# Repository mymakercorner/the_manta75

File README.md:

# The Manta75

The Manta75 is an exploded arrows and nav clusters 75% keyboard with a curvy bottom.
It is the second project of the *Sea Collection* and as such it's name is taken from one of the species we see in our oceans, the [Manta ray](https://en.wikipedia.org/wiki/Manta_ray).

The [Satisfaction 75](https://cannonkeys.com/collections/satisfaction-75) have this similar exploded arrows/nav clusters, on the manta75 I went with no knob and screen to maximize the number of available keys.

## Features

- Two pieces case designed with Fusion360.
- PCB designed with Kicad 5.1.5.
- Bottom mount leaf spring plate design with optional friction fit gaskets.
- [Unified C3 daughterboard](https://github.com/ai03-2725/Unified-Daughterboard)
- QMK firmware with VIA and VIAL support.

## Layout options

## Specifications

- Typing angle: 6 degrees
- Width: ~346mm
- Height: ~150mm
- Bezels size: 15mm all around.
- Front height: 18.3mm without bumpons, 19.7mm with bumpons.
- Top plate to top case distance: 7mm.
- Bumpons: 3M (reference SJ-5382). 
- Weight:
    - Aluminium top and bottom case: ~1,46Kg
    - Alumininum top and copper bottom case: ~4Kg
- Screws:
    - 6X M2.5x10 screws for top/bottom parts.
    - 4X M2.5x4 screws for plate/bottom parts.
    - 4X M2x4 screws for USB daughterboard. 

## Licensing 

[![CC BY 4.0][cc-by-shield]][cc-by]

Hardware design is provided under the very permissive
[Creative Commons Attribution 4.0 International License][cc-by].

[![CC BY 4.0][cc-by-image]][cc-by]

[cc-by]: http://creativecommons.org/licenses/by/4.0/
[cc-by-image]: https://licensebuttons.net/l/by/4.0/88x31.png
[cc-by-shield]: https://img.shields.io/badge/License-CC%20BY%204.0-lightgrey.svg

The goal is to allow anyone to use all hardware design files with the least restrictions possible.
This licence will allow you to make your own Manta75 and even use the hardware design files for commercial purposes.  

As for the QMK/VIA/VIAL firmware source code, it is provided on separate repositories, forks of QMK and QMK for Vial repositories.

## Design choices

### Layout

I wanted to type on the smallest layout possible but without sacrificing any usability for someone that has used no smaller than TKLs for a very long time.  

As a software engineer a keyboard is first and foremost a productivity instrument; as a result having arrow keys, nav keys and function keys without having to rely on layers is what I wanted.

75% layout seemed a good balance between compactness and usability, also wanted to separate arrow keys and nav cluster from the main keys.  
In the Manta75 you will find no screen, no knob and no badge, allowing to have a nav cluster of 5 keys instead of the usual 3 to 4 keys you can often find on other 75% keyboards. 

The goal ?  
Be able to use all my useful nav/arrow/function keys without having to rely on pressing a layer key.
The reason is that during programming sessions all those keys are already often used in combination with other mod keys (CTRL/SHIFT/ALT), adding a layer key press on top of that makes things difficult to manage (at least for me)

### Mounting

This is a leaf spring bottom mount design with only 4 fixation points.  
Having a bottom mount design makes installation of PCB/plate combo inside the case easy, even with the USB C daughterboard and JST cable. 

Gaskets can be optionally used below the leaves, friction fit placed in the bottom case.  
Length, position and material of the gaskets are up to personal preferences.
I personally uses Poron XRD of around 2cm length placed on the middle of the leaves, but it could be fun to play with other Poron types or even Sorbothane. 
No addhesive is needed to fix the gaskets as they are friction fit, the goal here is to be easily tuned to user preference and facilitate experimentation.

Physical simulations have been done in Fusion 360 to tune the thickness and length of the leaves.  
The result is a plate that is optimally tuned (to my taste) for aluminium material and that can be used without gaskets for maximum bounce.
For softer materials like FR4 the use of gaskets may be desirable.  

More details on plate design and Fusion 360 simulations can be found [HERE](PLATE_DESIGN.md).

### Case

#### Aestetics

There are 15mm bezels on all sides:
- I am a big sucker for thick bezels.
- This allowed me to accentuate the curvature on the bottom case significantly.
- Accentuating the bottom case curvature allows the screw holes not to be visible at side angles.

I wanted the bottom case to be very curvy with no obvious straight lines and to give the impression that the keyboard is floating on the desk, even from a side view of the board (the curvy bottom case helped a lot for that).

#### Functionality

The plate can move down up to 1.2mm, past that point it bottoms up on the bottom case to prevent excessive leaves distortion and switch pins shorting on the bottom case.  
There is a 1mm clearance between the plate and the top case for the plate to be able to tilt without touching it.   
There is 3.2mm clearance betweem PCB and bottom case so that the switch pins do not short the PCB when the plate is fully pressed.  
There are 4mm rails on the bottom case for optionally placing 3mm thick gaskets, those are loosely compressed by 0.2mm when the plate is assembled.

#### Machinability

Although quite curvy the case has been designed to be easily machined, even on a 3 axis CNC machine.
That does not mean it will be cheap to produce (those curves on the bottom case will take time to machine), more that there will be no big challenges for an average CNC manufacturer to make the case.

#### Picture galore

[Case renders](CASE_RENDERS.md)  
[Case received parts](CASE_PARTS.md)  
[Case photos](CASE_PHOTOS.md)

### PCB

The PCB is as simple as it can be:
- No RGB underglow.
- No per key lighting.
- Just the minimal features needed to have a stable working PCB for typing sessions.

This simplicity helped me a lot to achieve a goal that I wanted to pursue, an aestically pleasing PCB:
- Switch matrix column traces only on the top PCB.
- Switch matrix row traces and MCU traces only at the bottom PCB.
- Rounded traces with use of teardrops for switches holes.

To go further with aestetics I played with ground copper fills (only at the top PCB) and solder mask.  
This gives a bright solder mask color for the top of the PCB (because of the copper below it) and a darker solder mask color for the bottom of the PCB. This worked well on my green PCB prototypes and could work equally well for other semi-translucent solder mask colors like red, yellow, blue, violet, ...

To be user friendly all modifiers that can have different configurations are properly labelled on the silk screen. 

As for the manufacturing care has been taken it could easily be made and assembled at JLCPCB:
- All components references are from JLCPCB or it's sister company LCSC.
- Most are basic JLCPCB components to make the manufacturing cost as small as possible.
- Even the JST connector could be assembled if they happen to have some in stock (easy to solder yourself otherwise).

More details about the PCB can be found [HERE](PCB_DESIGN.md)  

## Making your own Manta75

### Risks

- Please note that all files and information here are to be used at your own risk.
- CNC manufacturing is not for the faint-hearted:
  - One-off CNC manufacturing is very expensive.
  - CNC manufacturers can make mistakes that can result in an expensive and useless chunk of metal.

### Case manufacturing

#### The data files

STEP files and drawings of top and bottom parts are available in *Case* directory.

The drawings, while far from professionally done, contains all requested information for the parts to be done by a CNC manufacturer: 
- Units used for the design (millimeters).
- Requested tolerance standard to be used during manufacturing (ISO 2768 - fine).
- All threaded holes are properly specified.
- Asked for deburring after machining.

#### About parts clearance

There is 0.15mm clearance between top and bottom parts.   
This allows to compensate for:
- CNC machining tolerancing errors.
- Parts finishing that can add to the part final thickness.

This clearance value is not universal, it's value depends on several factors:
- The confidance in your CNC manufacturer to target the given tolerance standard.
- The selected finish for earch part, each finish type adds more or less thickness to your final part.

A clearance of 0.15mm was for me suitable for the following finishing scenarios:
- Powdercoated top + raw bottom (tested).
- Powdercoated top + anodized type II bottom (not tested).
- Hard anodized type III top + raw or anodized type II bottom (not tested).
- Anodized type II top + raw or anodized type II bottom (not tested).

If you want to widen or tighten the clearance value, please do it by modifying the top case part only.

#### Selecting a CNC manufacturer

CNC services are getting more and more common nowadays:
- Some people uses 3DHubs.
- Others uses Xometry (I used Xometry EU for my Manta75 cases and for a previous project).
- Others uses Chinese manufacturers.

Please be aware that in general 'very cheap' and 'high quality' does not go well together.  
If price is a concern a solution to lower price per unit significantly is to make several units. Even doing 3 to 5 units will trop the price significantly.

### PCB manufacturing 

Kicad project is available in *Pcb/Kicad* directory.  

PCB fabrication files are available in *Pcb/Fabrication* directory.  
Those are:
- Gerber files.
- Bill of material (BOM) file.
- Pick and place (CPL) file for the assembly process.
Those are in the format that JLCPCB manufacturer expects, for you to very easily order assembled PCBs from them.
The files may need tweaking and/or modifications if you plan to go with other PCB manufacturers.   

### Plate manufacturing

Available plates data is available in *Plates* directory, both in DXF and STEP format.  
Two versions are available:
- ANSI.
- ISO.

ANSI only version gerber files of plate data for PCB manufacturing have also been added.  
Two versions are available:
- Gerber file for aluminium PCB manufacturing (tested).
- Gerber files for FR4 PCB manufacturing (untested).     

For those the layout options are limited to the following:
- 6.25u spacebar only.
- Left 1.25u CTRL/Win/ALT keys only.
- Right 1.5u CTRL/ALT keys only.
- Choice between standard or stepped Caps Lock.
- Choice between standard or split Backspace.

### QMK VIA/VIAL firmware

#### Source code repositories

QMK forked repository containing both default and VIA firmware source code for 'The Manta 75' is available at the following [link](https://github.com/mymakercorner/qmk_firmware/tree/the_manta75) in 'the_manta75' branch.

Vial-QMK forked repository containing both default VIA and VIAL firmware source code for 'The Manta 75' is available at the following  [link](https://github.com/mymakercorner/vial-qmk/tree/the_manta75) in 'the_manta75' branch.

#### Binaries

If you don't feel comfortable compiling QMK firmware yourself, brebuilt binaries for VIA and VIAL are available in the *Firmware* directory.  
VIA json file is also available to make the board recognised by VIA software.  
VIAL version of the firmware is compatible with both VIA and VIAL software.

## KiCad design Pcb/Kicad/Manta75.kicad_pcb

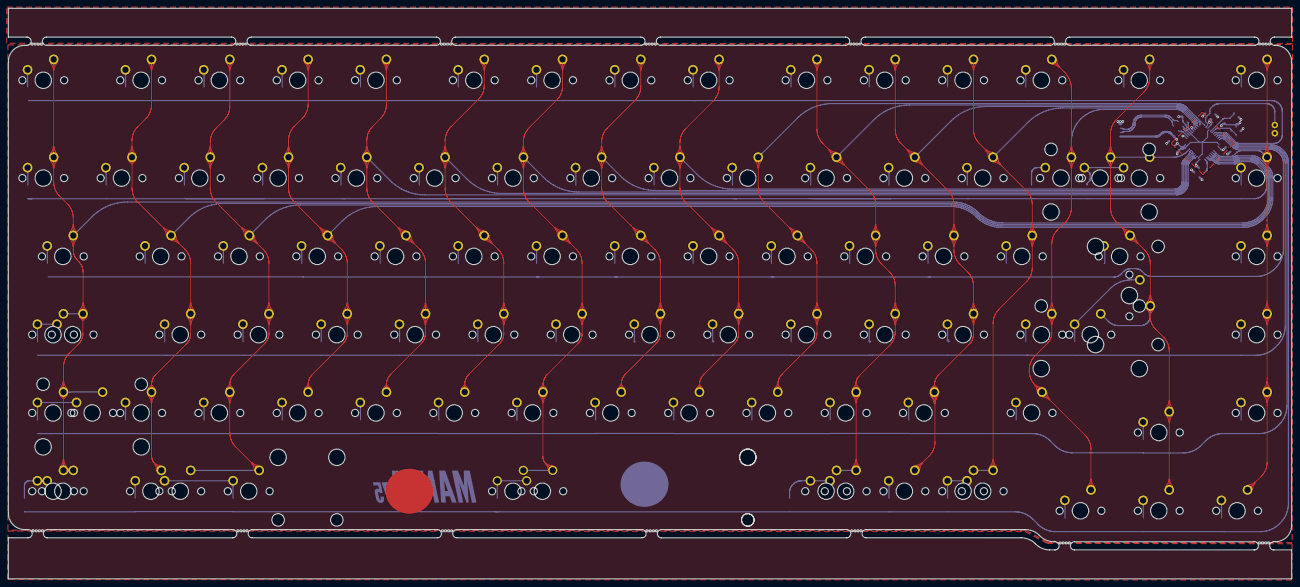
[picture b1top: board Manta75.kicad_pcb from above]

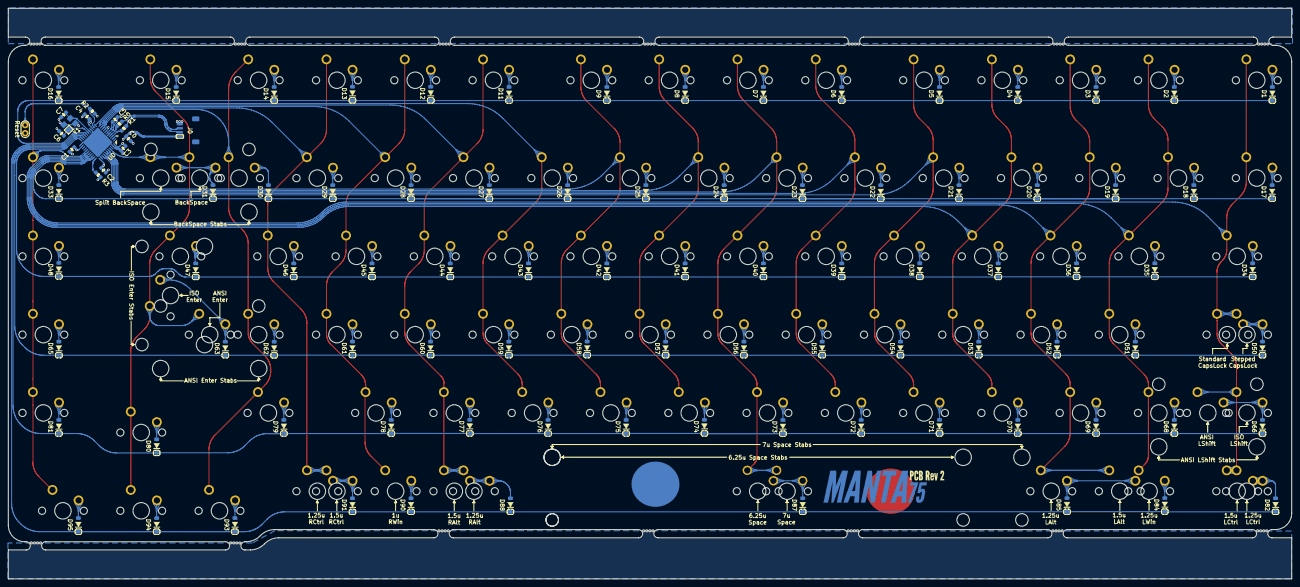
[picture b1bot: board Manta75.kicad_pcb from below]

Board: 2 copper layers, 312.3 x 138.8 mm, 201 parts (104 on the bottom side), 119 nets.

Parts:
C0: 10uF; Capacitor_603
C1, C2, C3, C4: 0.1uF; Capacitor_603
C5: 1uF; Capacitor_603
C6, C7: 8.2pF; Capacitor_603
D1, D2, D3, D4, D5, D6, D7, D8, D9, D11, D12, D13, D14, D15, D16, D17, D18, D19, D20, D21, D22, D23, D24, D25, D26, D27, D28, D29, D30, D31, D33, D34, D35, D36, D37, D38, D39, D40, D41, D42, D43, D44, D45, D46, D47, D48, D50, D51, D52, D53, D54, D55, D56, D57, D58, D59, D60, D61, D62, D63, D65, D66, D68, D69, D70, D71, D72, D73, D74, D75, D76, D77, D78, D79, D80, D81, D82, D84, D85, D87, D88, D90, D91, D93, D94, D95: D_Small; D_SOD-123
J0: JST SH; JST_SH_SM04B-SRSS-TB_1x04-1MP_P1.00mm_Horizontal
R0, R1: 22; Resistor_603
R2: 10K; Resistor_603
R3: 1K; Resistor_603
RST0: SW_Push; Reset_pins
Ref**: Val**; Vernes_Citation
Ref**#2, Ref**#3: Val**; Rico_Logo_Bright_Rev2
Ref**#4: Val**; Manta75_Logo_Bright_Rev2
SW1, SW2, SW3, SW4, SW5, SW6, SW7, SW8, SW9, SW11, SW12, SW13, SW14, SW15, SW16, SW17, SW18, SW19, SW20, SW21, SW22, SW23, SW24, SW25, SW26, SW27, SW28, SW29, SW30, SW32, SW33, SW35, SW36, SW37, SW38, SW39, SW40, SW41, SW42, SW43, SW44, SW45, SW46, SW48, SW51, SW52, SW53, SW54, SW55, SW56, SW57, SW58, SW59, SW60, SW61, SW62, SW65, SW68, SW69, SW70, SW71, SW72, SW73, SW74, SW75, SW76, SW77, SW78, SW80, SW81, SW88, SW90, SW91, SW93, SW94, SW95: SW_Push; Mx_Sw_1u
SW31: SW_Push; Mx_Sw_2u
SW34, SW47, SW83, SW86, SW89, SW92: SW_Push; Mx_Sw_15u
SW50, SW79: SW_Push; Mx_Sw_175u
SW63, SW67: SW_Push; Mx_Sw_225u
SW64: SW_Push; Mx_Sw_Iso
SW66, SW82, SW84, SW85: SW_Push; Mx_Sw_125u
SW87: SW_Push; Mx_Sw_625u_North_Stab
SW96: SW_Push; Mx_Sw_7u_North_Stab
SW97: SW_Push; Mx_Sw_Stepped_175u
U0: ATmega32U4-MU; QFN-44-1EP_7x7mm_P0.5mm_EP5.2x5.2mm
Y1: Crystal_16MHz; Crystal_SMD_3225-4Pin_3.2x2.5mm

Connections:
+5V: C0.1, C1.1, C2.1, C3.1, C4.1, J0.1, R2.2, U0.2, U0.7, U0.14, U0.24, U0.34, U0.44
Col0: SW1.2, SW17.2, SW34.2, SW50.2, SW66.2, SW67.2, SW82.2, SW83.2, SW97.2, U0.31
Col1: SW2.2, SW18.2, SW35.2, SW51.2, SW68.2, SW84.2, U0.30
Col2: SW3.2, SW19.2, SW36.2, SW52.2, SW69.2, SW85.2, SW86.2, U0.29
Col3: SW4.2, SW20.2, SW37.2, SW53.2, SW70.2, U0.28
Col4: SW5.2, SW21.2, SW38.2, SW54.2, SW71.2, U0.36
Col5: SW6.2, SW22.2, SW39.2, SW55.2, SW72.2, U0.37
Col6: SW7.2, SW23.2, SW40.2, SW56.2, SW73.2, SW87.2, SW96.2, U0.38
Col7: SW8.2, SW24.2, SW41.2, SW57.2, SW74.2, U0.39
Col8: SW9.2, SW25.2, SW42.2, SW58.2, SW75.2, U0.40
Col9: SW26.2, SW43.2, SW59.2, SW76.2, U0.12
Col10: SW11.2, SW27.2, SW44.2, SW60.2, SW77.2, SW88.2, SW89.2, U0.11
Col11: SW12.2, SW28.2, SW45.2, SW61.2, SW78.2, SW90.2, U0.10
Col12: SW13.2, SW29.2, SW46.2, SW91.2, SW92.2, U0.9
Col13: SW14.2, SW30.2, SW62.2, SW79.2, SW93.2, U0.8
Col14: SW15.2, SW31.2, SW32.2, SW47.2, SW63.2, SW64.2, SW80.2, SW94.2, U0.41
Col15: SW16.2, SW33.2, SW48.2, SW65.2, SW81.2, SW95.2, U0.27
D+: J0.3, R0.2
D-: J0.2, R1.2
GND: C0.2, C1.2, C2.2, C3.2, C4.2, C5.2, C6.2, C7.2, J0.4, R3.1, RST0.2, U0.5, U0.15, U0.23, U0.35, U0.43, U0.45, Y1.2, Y1.4
unnamed: C5.1, U0.6
unnamed: C6.1, U0.17, Y1.1
unnamed: C7.1, U0.16, Y1.3
unnamed: D1.2, SW1.1
unnamed: D2.2, SW2.1
unnamed: D3.2, SW3.1
unnamed: D4.2, SW4.1
unnamed: D5.2, SW5.1
unnamed: D6.2, SW6.1
unnamed: D7.2, SW7.1
unnamed: D8.2, SW8.1
unnamed: D9.2, SW9.1
unnamed: D11.2, SW11.1
unnamed: D12.2, SW12.1
unnamed: D13.2, SW13.1
unnamed: D14.2, SW14.1
unnamed: D15.2, SW15.1
unnamed: D16.2, SW16.1
unnamed: D17.2, SW17.1
unnamed: D18.2, SW18.1
unnamed: D19.2, SW19.1
unnamed: D20.2, SW20.1
unnamed: D21.2, SW21.1
unnamed: D22.2, SW22.1
unnamed: D23.2, SW23.1
unnamed: D24.2, SW24.1
unnamed: D25.2, SW25.1
unnamed: D26.2, SW26.1
unnamed: D27.2, SW27.1
unnamed: D28.2, SW28.1
unnamed: D29.2, SW29.1
unnamed: D30.2, SW30.1
unnamed: D31.2, SW31.1, SW32.1
unnamed: D33.2, SW33.1
unnamed: D34.2, SW34.1
unnamed: D35.2, SW35.1
unnamed: D36.2, SW36.1
unnamed: D37.2, SW37.1
unnamed: D38.2, SW38.1
unnamed: D39.2, SW39.1
unnamed: D40.2, SW40.1
unnamed: D41.2, SW41.1
unnamed: D42.2, SW42.1
unnamed: D43.2, SW43.1
unnamed: D44.2, SW44.1
unnamed: D45.2, SW45.1
unnamed: D46.2, SW46.1
unnamed: D47.2, SW47.1
unnamed: D48.2, SW48.1
unnamed: D50.2, SW50.1, SW97.1
unnamed: D51.2, SW51.1
unnamed: D52.2, SW52.1
unnamed: D53.2, SW53.1
unnamed: D54.2, SW54.1
unnamed: D55.2, SW55.1
unnamed: D56.2, SW56.1
unnamed: D57.2, SW57.1
unnamed: D58.2, SW58.1
unnamed: D59.2, SW59.1
unnamed: D60.2, SW60.1
unnamed: D61.2, SW61.1
unnamed: D62.2, SW62.1
unnamed: D63.2, SW63.1, SW64.1
unnamed: D65.2, SW65.1
unnamed: D66.2, SW66.1, SW67.1
unnamed: D68.2, SW68.1
unnamed: D69.2, SW69.1
unnamed: D70.2, SW70.1
unnamed: D71.2, SW71.1
unnamed: D72.2, SW72.1
unnamed: D73.2, SW73.1
unnamed: D74.2, SW74.1
unnamed: D75.2, SW75.1
unnamed: D76.2, SW76.1
unnamed: D77.2, SW77.1
unnamed: D78.2, SW78.1
unnamed: D79.2, SW79.1
unnamed: D80.2, SW80.1
unnamed: D81.2, SW81.1
unnamed: D82.2, SW82.1, SW83.1
unnamed: D84.2, SW84.1
unnamed: D85.2, SW85.1, SW86.1
unnamed: D87.2, SW87.1, SW96.1
unnamed: D88.2, SW88.1, SW89.1
unnamed: D90.2, SW90.1
unnamed: D91.2, SW91.1, SW92.1
unnamed: D93.2, SW93.1
unnamed: D94.2, SW94.1
unnamed: D95.2, SW95.1
unnamed: R0.1, U0.4
unnamed: R1.1, U0.3
unnamed: R3.2, U0.33
Reset: R2.1, RST0.1, U0.13
Row0: D1.1, D2.1, D3.1, D4.1, D5.1, D6.1, D7.1, D8.1, D9.1, D11.1, D12.1, D13.1, D14.1, D15.1, D16.1, U0.18
Row1: D17.1, D18.1, D19.1, D20.1, D21.1, D22.1, D23.1, D24.1, D25.1, D26.1, D27.1, D28.1, D29.1, D30.1, D31.1, D33.1, U0.32
Row2: D34.1, D35.1, D36.1, D37.1, D38.1, D39.1, D40.1, D41.1, D42.1, D43.1, D44.1, D45.1, D46.1, D47.1, D48.1, U0.22
Row3: D50.1, D51.1, D52.1, D53.1, D54.1, D55.1, D56.1, D57.1, D58.1, D59.1, D60.1, D61.1, D62.1, D63.1, D65.1, U0.21
Row4: D66.1, D68.1, D69.1, D70.1, D71.1, D72.1, D73.1, D74.1, D75.1, D76.1, D77.1, D78.1, D79.1, D80.1, D81.1, U0.20
Row5: D82.1, D84.1, D85.1, D87.1, D88.1, D90.1, D91.1, D93.1, D94.1, D95.1, U0.19

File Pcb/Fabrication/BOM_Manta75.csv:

Comment,Designator, Footprint, LCSC Part Number
10uF,C0 ,Rico:Capacitor_603,C19702
0.1uF,C1 C2 C3 C4 ,Rico:Capacitor_603,C14663
1uF,C5 ,Rico:Capacitor_603,C15849
8.2pF,C7 C6 ,Rico:Capacitor_603,C1685
D_Small,D1 D2 D3 D4 D5 D6 D7 D8 D9 D11 D12 D13 D14 D15 D16 D17 D18 D19 D20 D21 D22 D23 D24 D25 D26 D27 D28 D29 D31 D33 D34 D35 D36 D37 D38 D39 D40 D41 D42 D43 D44 D45 D47 D48 D46 D50 D51 D52 D53 D54 D55 D56 D57 D58 D59 D60 D61 D62 D63 D65 D66 D68 D69 D70 D71 D72 D73 D74 D75 D76 D77 D78 D79 D80 D81 D82 D84 D85 D87 D93 D94 D95 D30 D91 D90 D88 ,Rico:D_SOD-123,C81598
JST SH,J0 ,Rico:JST_SH_SM04B-SRSS-TB_1x04-1MP_P1.00mm_Horizontal,C160404
22,R0 R1 ,Rico:Resistor_603,C23345
10K,R2 ,Rico:Resistor_603,C25804
1K,R3 ,Rico:Resistor_603,C21190
ATmega32U4-MU,U0 ,Rico:QFN-44-1EP_7x7mm_P0.5mm_EP5.2x5.2mm,C45874
Crystal_16MHz,Y1 ,Rico:Crystal_SMD_3225-4Pin_3.2x2.5mm, C13738

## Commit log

2022-01-23 [feature] Creation of the manta75 project
2022-01-23 [cleanup] Fixed few typo errors in the readme
2022-03-11 [feature] Added gerber files for plate PCB manufacturing, added screws specification in readme file.
